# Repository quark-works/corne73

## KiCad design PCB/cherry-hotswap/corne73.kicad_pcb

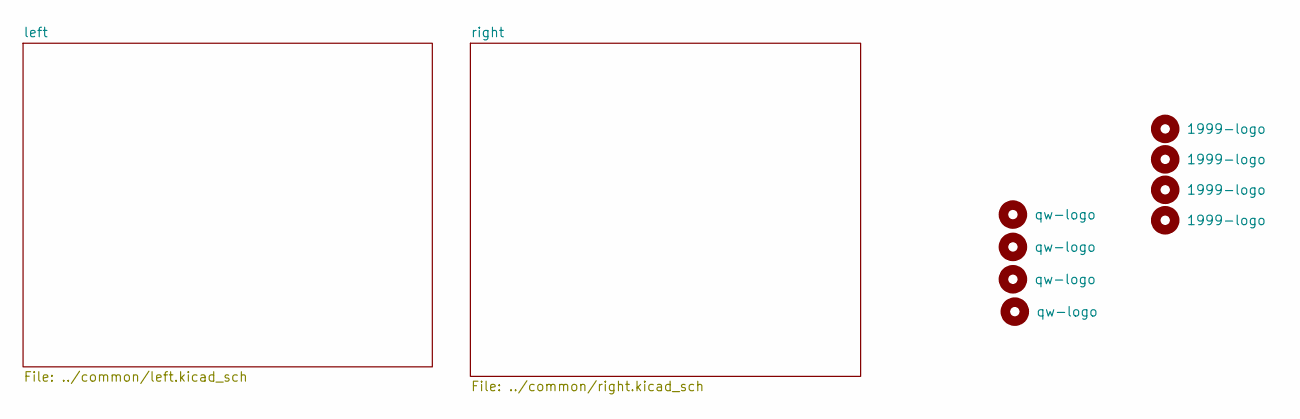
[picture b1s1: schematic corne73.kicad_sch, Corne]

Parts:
H1, H2, H3, H4: qw-logo; qw new logo silk + copper sm
H5, H6, H7, H8: 1999-logo; 1999 logo md

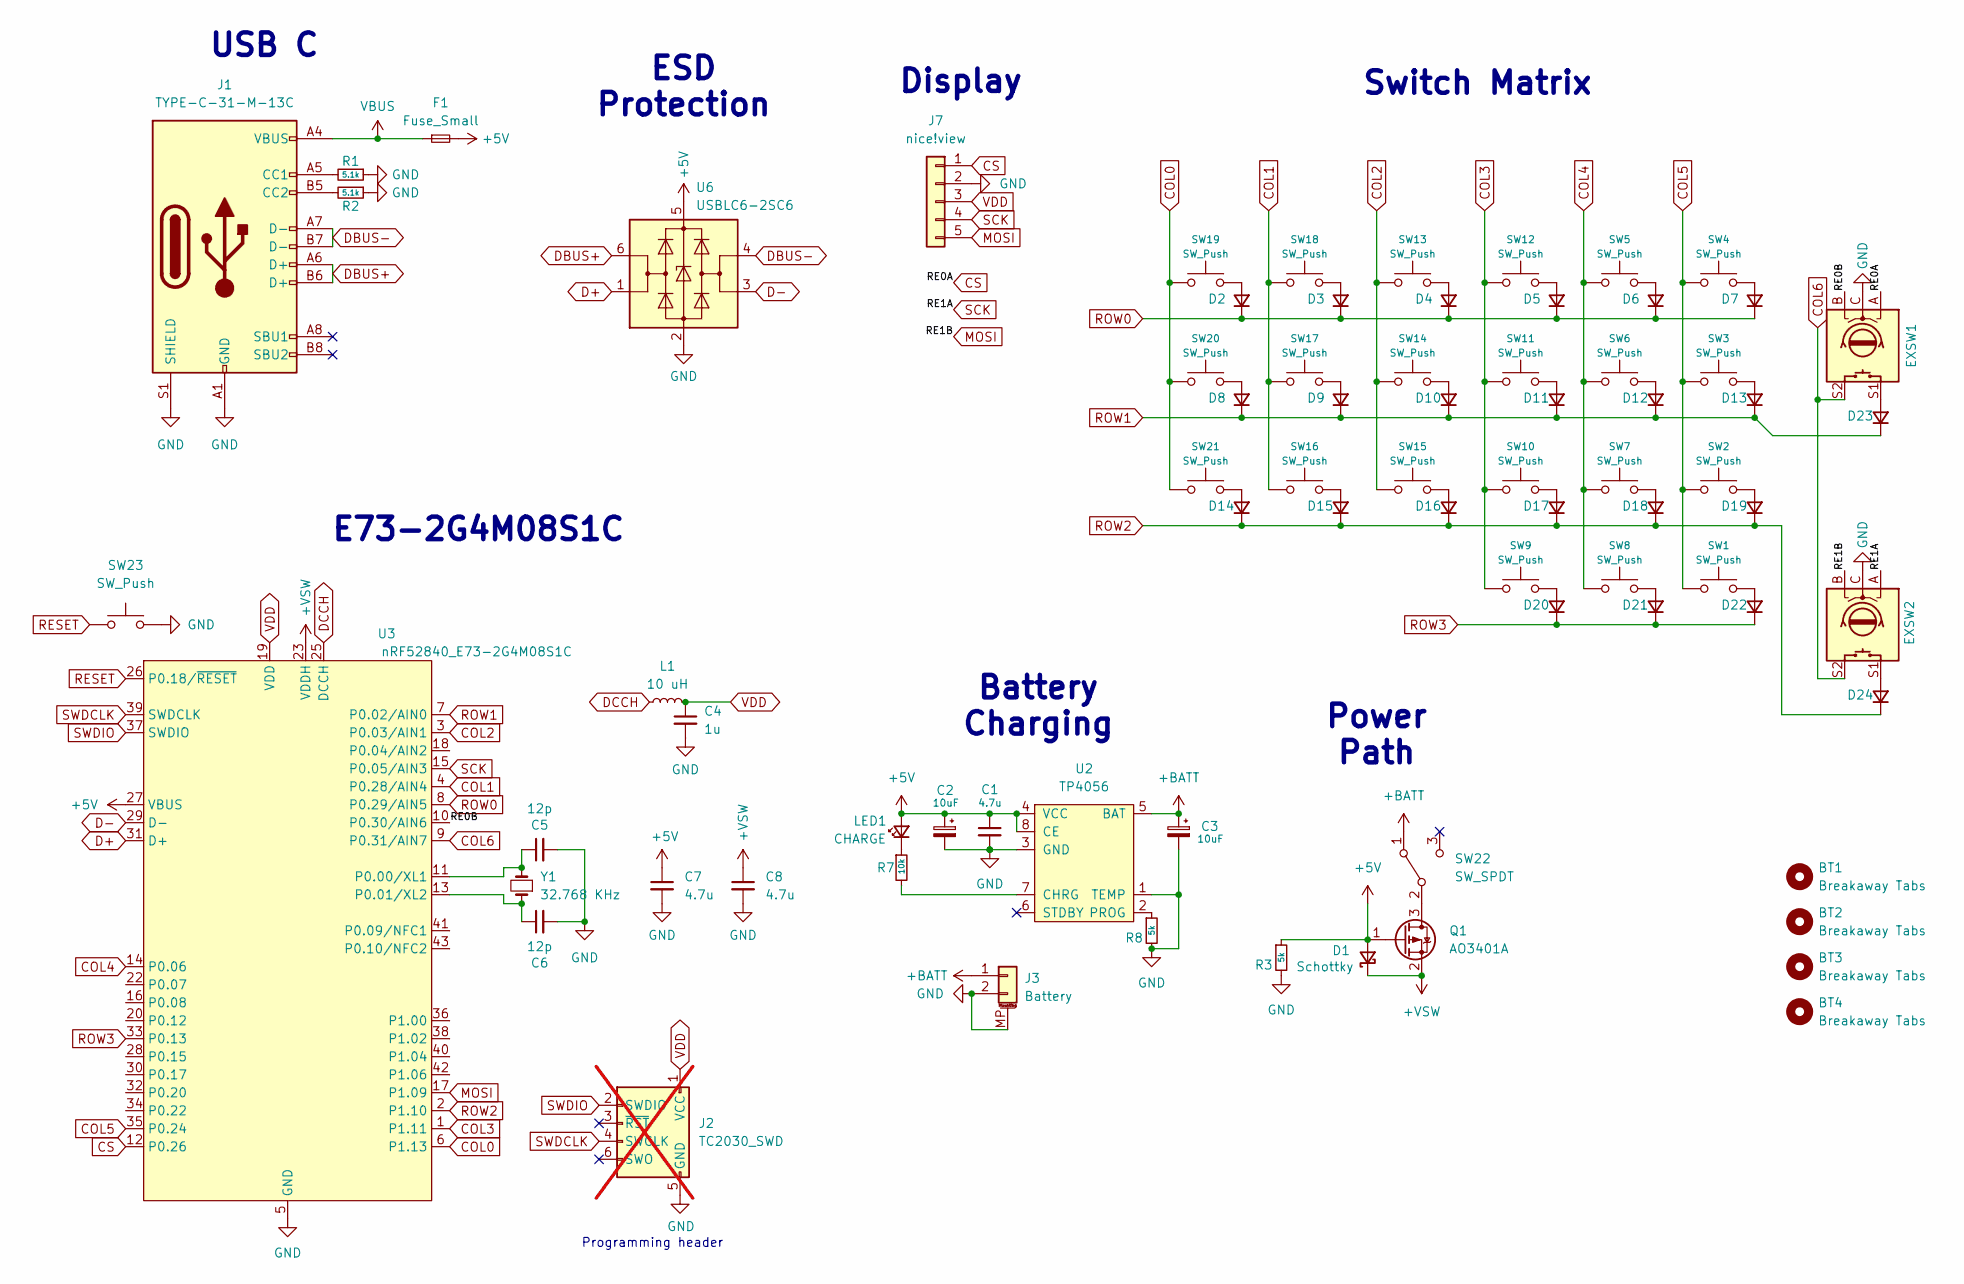
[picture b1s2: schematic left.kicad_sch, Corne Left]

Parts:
BT1, BT2, BT3, BT4: Breakaway Tabs; Breakaway_Tabs
C1, C7, C8: 4.7u; C_0603_1608Metric
C2, C3: 10uF; CP_EIA-2012-12_Kemet-R
C4: 1u; C_0603_1608Metric
C5, C6: 12p; C_0603_1608Metric
D1: Schottky; D_SOD-123
D2, D3, D4, D5, D6, D7, D8, D9, D10, D11, D12, D13, D14, D15, D16, D17, D18, D19, D20, D21, D22, D23, D24: 1N4148; D_SOD-123
EXSW1, EXSW2: RotaryEncoder_Switch; SwitchCombo+Encoder
F1: Fuse_Small; Fuse_1206_3216Metric
J1: TYPE-C-31-M-13C; JLCPCB Part # C2848620
J2: TC2030_SWD; CON_TC2030_outlined; not fitted
J3: Battery; Molex_Pico-EZmate_78171-0002_1x02-1MP_P1.20mm_Vertical
J7: nice!view; PinHeader_1x05_P2.54mm_Vertical
L1: 10 uH; L_0603_1608Metric; LCSC C92982
LED1: CHARGE; LED_0805_2012Metric
Q1: AO3401A; SOT-23
R1, R2: 5.1k; R_0402_1005Metric
R3, R8: 5k; R_0603_1608Metric
R7: 10k; R_0603_1608Metric
SW1, SW2, SW3, SW4, SW5, SW6, SW7, SW8, SW9, SW10, SW11, SW12, SW13, SW14, SW15, SW16, SW17, SW18, SW19, SW20, SW21: SW_Push; SwitchCombo
SW22: SW_SPDT; SW_SPDT_PCM12; LCSC C136720
SW23: SW_Push; SW_T1A2QR
U2: TP4056; CustomTP4056; LCSC C16581
U3: nRF52840_E73-2G4M08S1C; LCSC C356849
U6: USBLC6-2SC6; SOT-23-6
Y1: 32.768 KHz; Crystal_SMD_2012-2Pin_2.0x1.2mm; LCSC C55208

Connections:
+5V: C1.1, C2.1, C7.1, D1.2 (A), F1.2, LED1.2 (A), Q1.1 (G), R3.1, U2.4 (VCC), U2.8 (CE), U3.27 (VBUS), U6.5 (VBUS)
+BATT: C3.1, J3.1, SW22.1 (A), U2.5 (BAT)
+VSW: C8.1, D1.1 (K), Q1.2 (S), U3.23 (VDDH)
/left/RE0B: EXSW1.B, U3.10 (P0.30/AIN6)
COL0: SW19.2, SW20.2, SW21.2, U3.6 (P1.13)
COL1: SW16.2, SW17.2, SW18.2, U3.4 (P0.28/AIN4)
COL2: SW13.2, SW14.2, SW15.2, U3.3 (P0.03/AIN1)
COL3: SW9.2, SW10.2, SW11.2, SW12.2, U3.1 (P1.11)
COL4: SW5.2, SW6.2, SW7.2, SW8.2, U3.14 (P0.06)
COL5: SW1.2, SW2.2, SW3.2, SW4.2, U3.35 (P0.24)
COL6: EXSW1.S2, EXSW2.S2, U3.9 (P0.31/AIN7)
CS: EXSW1.A, J7.1, U3.12 (P0.26)
D+: U3.31 (D+), U6.1 (I/O1)
D-: U3.29 (D-), U6.3 (I/O2)
DBUS+: J1.A6 (D+), J1.B6 (D+), U6.6 (I/O1)
DBUS-: J1.A7 (D-), J1.B7 (D-), U6.4 (I/O2)
DCCH: L1.1, U3.25 (DCCH)
GND: C1.2, C2.2, C3.2, C4.2, C5.2, C6.2, C7.2, C8.2, EXSW1.C, EXSW2.C, J1.A1 (GND), J1.A12 (GND), J1.B1 (GND), J1.B12 (GND), J1.S1 (SHIELD), J2.5 (GND), J3.2, J3.MP (MountPin), J7.2, R1.1, R2.1, R3.2, R8.2, SW23.2, U2.1 (TEMP), U2.3 (GND), U3.5 (GND), U3.21 (GND), U3.24 (GND), U6.2 (GND)
MOSI: EXSW2.B, J7.5, U3.17 (P1.09)
unnamed: D2.2 (A), SW19.1
unnamed: D3.2 (A), SW18.1
unnamed: D4.2 (A), SW13.1
unnamed: D5.2 (A), SW12.1
unnamed: D6.2 (A), SW5.1
unnamed: D7.2 (A), SW4.1
unnamed: D8.2 (A), SW20.1
unnamed: D9.2 (A), SW17.1
unnamed: D10.2 (A), SW14.1
unnamed: D11.2 (A), SW11.1
unnamed: D12.2 (A), SW6.1
unnamed: D13.2 (A), SW3.1
unnamed: D14.2 (A), SW21.1
unnamed: D15.2 (A), SW16.1
unnamed: D16.2 (A), SW15.1
unnamed: D17.2 (A), SW10.1
unnamed: D18.2 (A), SW7.1
unnamed: D19.2 (A), SW2.1
unnamed: D20.2 (A), SW9.1
unnamed: D21.2 (A), SW8.1
unnamed: D22.2 (A), SW1.1
unnamed: D23.2 (A), EXSW1.S1
unnamed: D24.2 (A), EXSW2.S1
unnamed: J1.A5 (CC1), R1.2
unnamed: J1.B5 (CC2), R2.2
unnamed: LED1.1 (K), R7.1
unnamed: Q1.3 (D), SW22.2 (B)
unnamed: R7.2, U2.7 (CHRG)
unnamed: R8.1, U2.2 (PROG)
unnamed: C5.1, U3.11 (P0.00/XL1), Y1.2
unnamed: C6.1, U3.13 (P0.01/XL2), Y1.1
RESET: SW23.1, U3.26 (P0.18/~RESET)
ROW0: D2.1 (K), D3.1 (K), D4.1 (K), D5.1 (K), D6.1 (K), D7.1 (K), U3.8 (P0.29/AIN5)
ROW1: D8.1 (K), D9.1 (K), D10.1 (K), D11.1 (K), D12.1 (K), D13.1 (K), D23.1 (K), U3.7 (P0.02/AIN0)
ROW2: D14.1 (K), D15.1 (K), D16.1 (K), D17.1 (K), D18.1 (K), D19.1 (K), D24.1 (K), U3.2 (P1.10)
ROW3: D20.1 (K), D21.1 (K), D22.1 (K), U3.33 (P0.13)
SCK: EXSW2.A, J7.4, U3.15 (P0.05/AIN3)
SWDCLK: J2.4 (SWCLK), U3.39 (SWDCLK)
SWDIO: J2.2 (SWDIO), U3.37 (SWDIO)
VBUS: F1.1, J1.A4 (VBUS), J1.A9 (VBUS), J1.B4 (VBUS), J1.B9 (VBUS)
VDD: C4.1, J2.1 (VCC), J7.3, L1.2, U3.19 (VDD)

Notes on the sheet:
Display
Power Path
USB C
Battery Charging
Programming header
E73-2G4M08S1C
Switch Matrix
ESD Protection

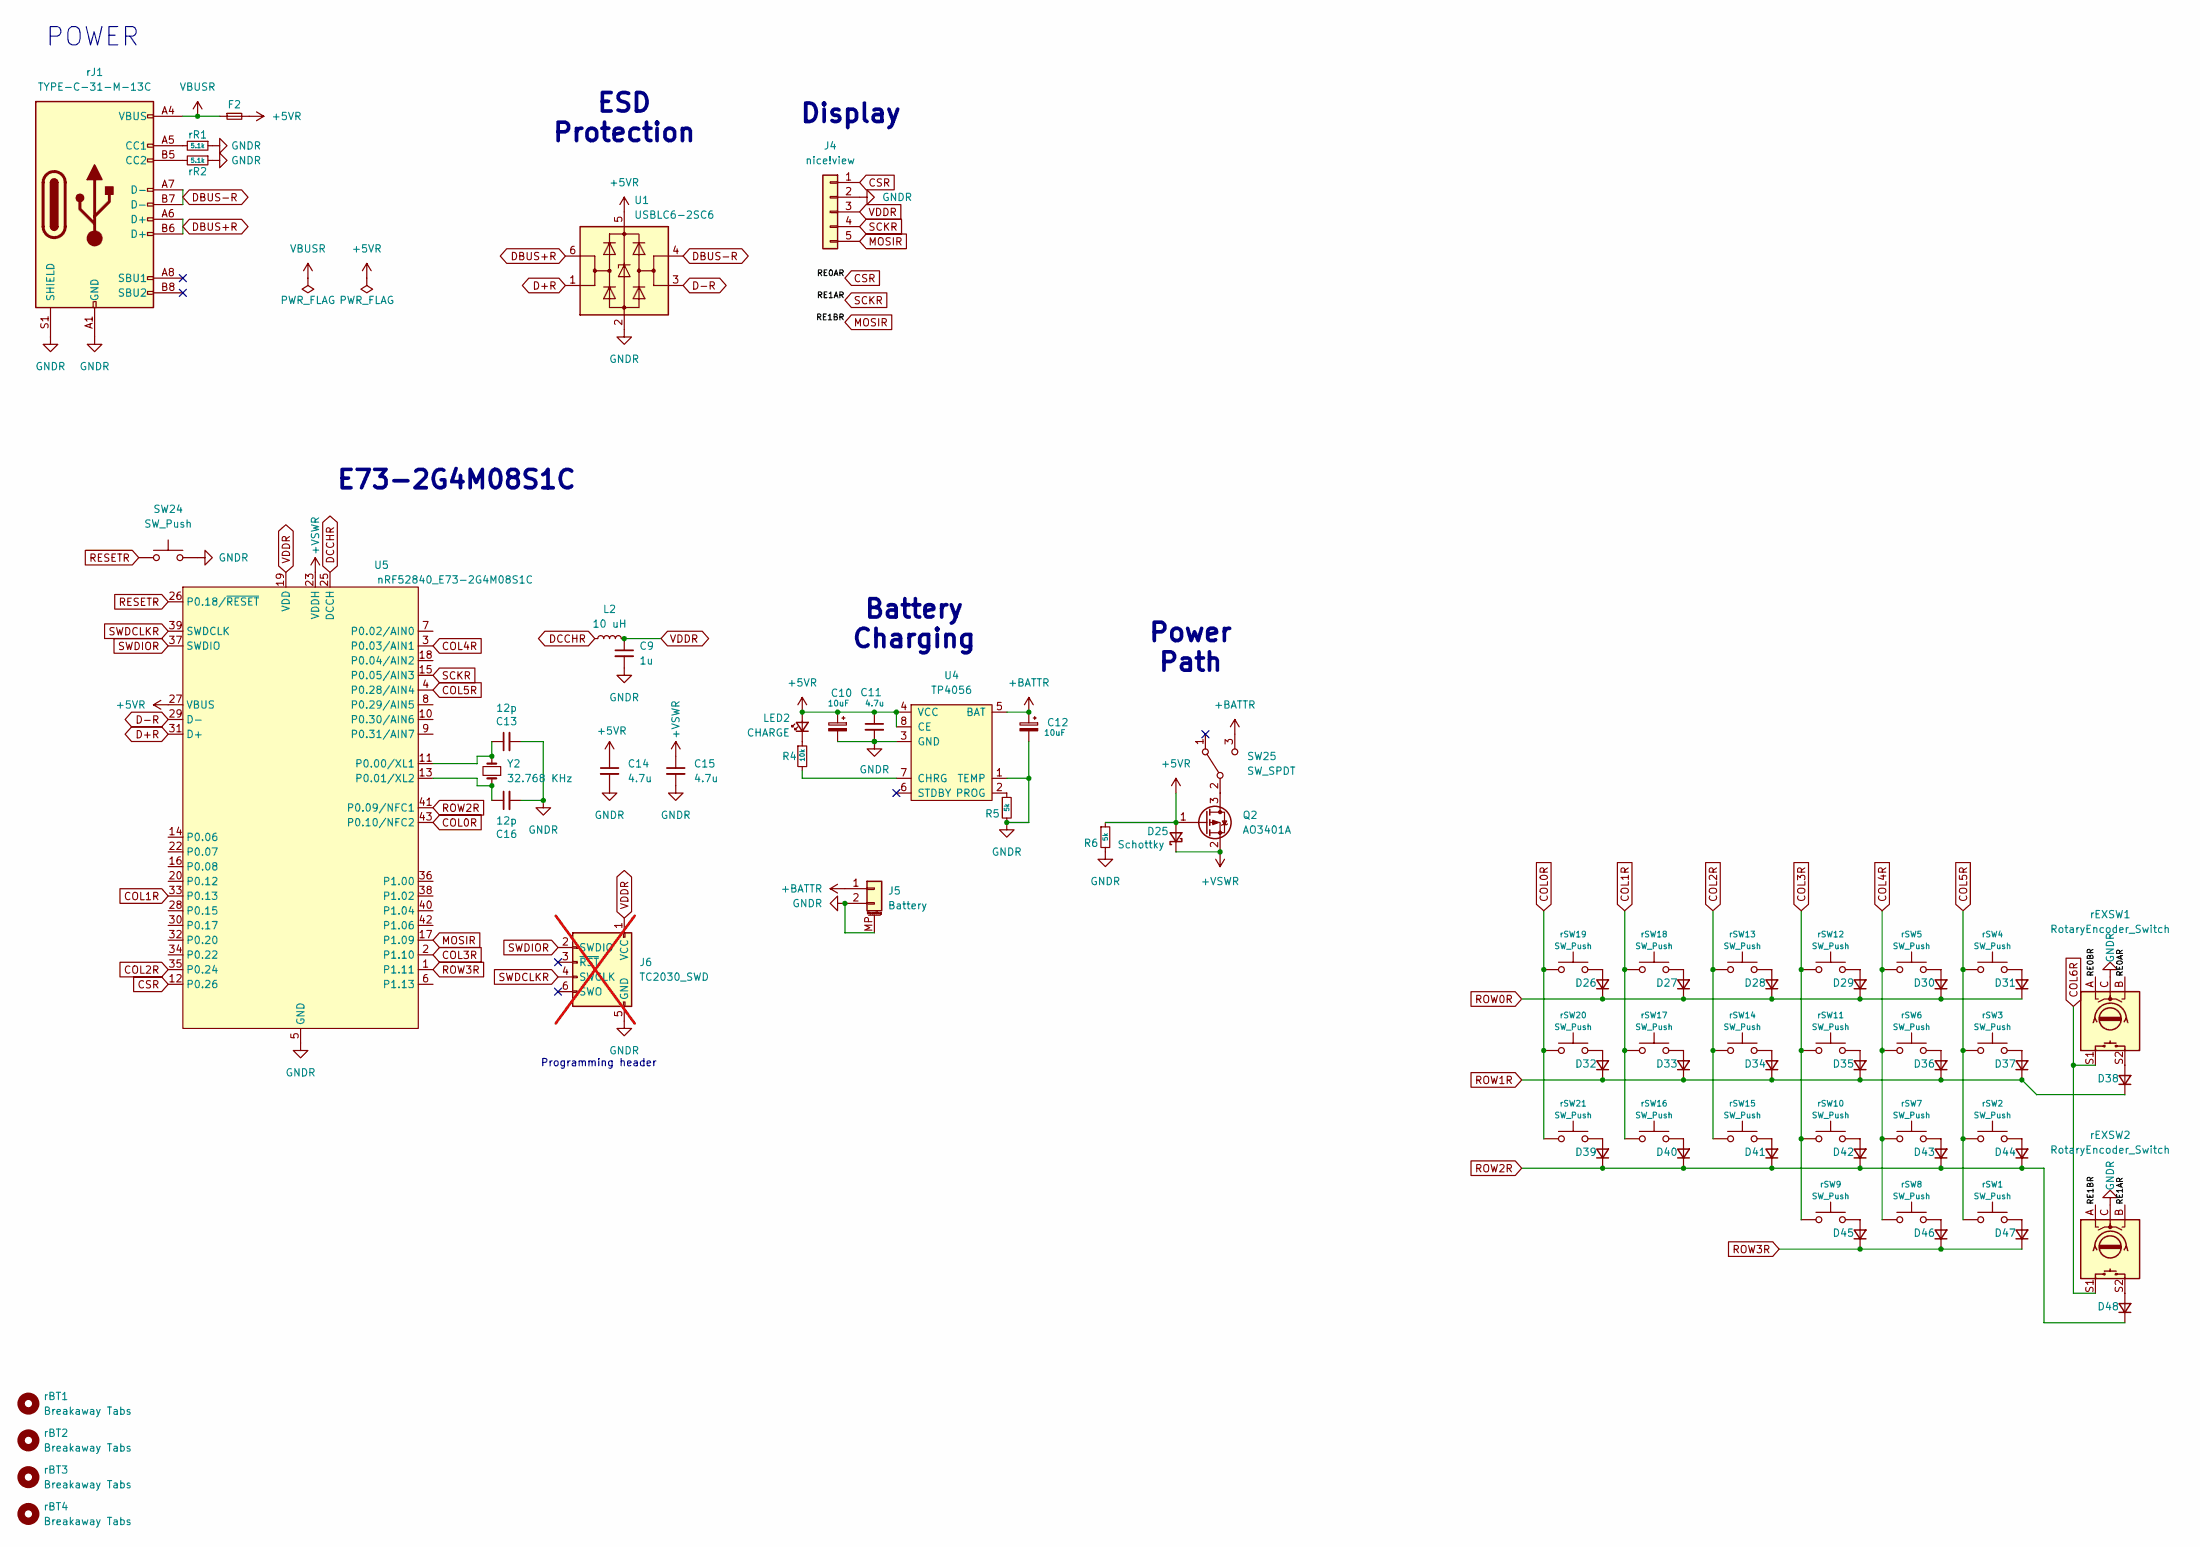
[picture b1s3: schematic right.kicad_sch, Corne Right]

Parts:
C9: 1u; C_0603_1608Metric
C10, C12: 10uF; CP_EIA-2012-12_Kemet-R
C11, C14, C15: 4.7u; C_0603_1608Metric
C13, C16: 12p; C_0603_1608Metric
D25: Schottky; D_SOD-123
D26, D27, D28, D29, D30, D31, D32, D33, D34, D35, D36, D37, D38, D39, D40, D41, D42, D43, D44, D45, D46, D47, D48: 1N4148; D_SOD-123
F2: Fuse_Small; Fuse_1206_3216Metric
J4: nice!view; PinHeader_1x05_P2.54mm_Vertical
J5: Battery; Molex_Pico-EZmate_78171-0002_1x02-1MP_P1.20mm_Vertical
J6: TC2030_SWD; CON_TC2030_outlined; not fitted
L2: 10 uH; L_0603_1608Metric; LCSC C92982
LED2: CHARGE; LED_0805_2012Metric
Q2: AO3401A; SOT-23
R4: 10k; R_0603_1608Metric
R5, R6: 5k; R_0603_1608Metric
SW24: SW_Push; SW_T1A2QR
SW25: SW_SPDT; SW_SPDT_PCM12; LCSC C136720
U1: USBLC6-2SC6; SOT-23-6
U4: TP4056; CustomTP4056; LCSC C16581
U5: nRF52840_E73-2G4M08S1C; LCSC C356849
Y2: 32.768 KHz; Crystal_SMD_2012-2Pin_2.0x1.2mm; LCSC C55208
rBT1, rBT2, rBT3, rBT4: Breakaway Tabs; Breakaway_Tabs
rEXSW1, rEXSW2: RotaryEncoder_Switch; SwitchCombo+Encoder
rJ1: TYPE-C-31-M-13C; JLCPCB Part # C2848620
rR1, rR2: 5.1k; R_0402_1005Metric
rSW1, rSW2, rSW3, rSW4, rSW5, rSW6, rSW7, rSW8, rSW9, rSW10, rSW11, rSW12, rSW13, rSW14, rSW15, rSW16, rSW17, rSW18, rSW19, rSW20, rSW21: SW_Push; SwitchCombo

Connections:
+5VR: C10.1, C11.1, C14.1, D25.2 (A), F2.2, LED2.2 (A), Q2.1 (G), R6.1, U1.5 (VBUS), U4.4 (VCC), U4.8 (CE), U5.27 (VBUS)
+BATTR: C12.1, J5.1, SW25.3 (C), U4.5 (BAT)
+VSWR: C15.1, D25.1 (K), Q2.2 (S), U5.23 (VDDH)
/right/RE0BR: rEXSW1.A
COL0R: U5.43 (P0.10/NFC2), rSW19.2, rSW20.2, rSW21.2
COL1R: U5.33 (P0.13), rSW16.2, rSW17.2, rSW18.2
COL2R: U5.35 (P0.24), rSW13.2, rSW14.2, rSW15.2
COL3R: U5.2 (P1.10), rSW9.2, rSW10.2, rSW11.2, rSW12.2
COL4R: U5.3 (P0.03/AIN1), rSW5.2, rSW6.2, rSW7.2, rSW8.2
COL5R: U5.4 (P0.28/AIN4), rSW1.1, rSW2.2, rSW3.2, rSW4.2
COL6R: rEXSW1.S1, rEXSW2.S1
CSR: J4.1, U5.12 (P0.26), rEXSW1.B
D+R: U1.1 (I/O1), U5.31 (D+)
D-R: U1.3 (I/O2), U5.29 (D-)
DBUS+R: U1.6 (I/O1), rJ1.A6 (D+), rJ1.B6 (D+)
DBUS-R: U1.4 (I/O2), rJ1.A7 (D-), rJ1.B7 (D-)
DCCHR: L2.1, U5.25 (DCCH)
GNDR: C9.2, C10.2, C11.2, C12.2, C13.2, C14.2, C15.2, C16.2, J4.2, J5.2, J5.MP (MountPin), J6.5 (GND), R5.2, R6.2, SW24.2, U1.2 (GND), U4.1 (TEMP), U4.3 (GND), U5.5 (GND), U5.21 (GND), U5.24 (GND), rEXSW1.C, rEXSW2.C, rJ1.A1 (GND), rJ1.A12 (GND), rJ1.B1 (GND), rJ1.B12 (GND), rJ1.S1 (SHIELD), rR1.1, rR2.1
MOSIR: J4.5, U5.17 (P1.09), rEXSW2.A
unnamed: D26.2 (A), rSW19.1
unnamed: D27.2 (A), rSW18.1
unnamed: D28.2 (A), rSW13.1
unnamed: D29.2 (A), rSW12.1
unnamed: D30.2 (A), rSW5.1
unnamed: D31.2 (A), rSW4.1
unnamed: D32.2 (A), rSW20.1
unnamed: D33.2 (A), rSW17.1
unnamed: D34.2 (A), rSW14.1
unnamed: D35.2 (A), rSW11.1
unnamed: D36.2 (A), rSW6.1
unnamed: D37.2 (A), rSW3.1
unnamed: D38.2 (A), rEXSW1.S2
unnamed: D39.2 (A), rSW21.1
unnamed: D40.2 (A), rSW16.1
unnamed: D41.2 (A), rSW15.1
unnamed: D42.2 (A), rSW10.1
unnamed: D43.2 (A), rSW7.1
unnamed: D44.2 (A), rSW2.1
unnamed: D45.2 (A), rSW9.1
unnamed: D46.2 (A), rSW8.1
unnamed: D47.2 (A), rSW1.2
unnamed: D48.2 (A), rEXSW2.S2
unnamed: LED2.1 (K), R4.1
unnamed: Q2.3 (D), SW25.2 (B)
unnamed: R4.2, U4.7 (CHRG)
unnamed: R5.1, U4.2 (PROG)
unnamed: C13.1, U5.11 (P0.00/XL1), Y2.2
unnamed: C16.1, U5.13 (P0.01/XL2), Y2.1
unnamed: rJ1.A5 (CC1), rR1.2
unnamed: rJ1.B5 (CC2), rR2.2
RESETR: SW24.1, U5.26 (P0.18/~RESET)
ROW0R: D26.1 (K), D27.1 (K), D28.1 (K), D29.1 (K), D30.1 (K), D31.1 (K)
ROW1R: D32.1 (K), D33.1 (K), D34.1 (K), D35.1 (K), D36.1 (K), D37.1 (K), D38.1 (K)
ROW2R: D39.1 (K), D40.1 (K), D41.1 (K), D42.1 (K), D43.1 (K), D44.1 (K), D48.1 (K), U5.41 (P0.09/NFC1)
ROW3R: D45.1 (K), D46.1 (K), D47.1 (K), U5.1 (P1.11)
SCKR: J4.4, U5.15 (P0.05/AIN3), rEXSW2.B
SWDCLKR: J6.4 (SWCLK), U5.39 (SWDCLK)
SWDIOR: J6.2 (SWDIO), U5.37 (SWDIO)
VBUSR: F2.1, rJ1.A4 (VBUS), rJ1.A9 (VBUS), rJ1.B4 (VBUS), rJ1.B9 (VBUS)
VDDR: C9.1, J4.3, J6.1 (VCC), L2.2, U5.19 (VDD)

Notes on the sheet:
Display
Power Path
POWER
Battery Charging
E73-2G4M08S1C
Programming header
ESD Protection

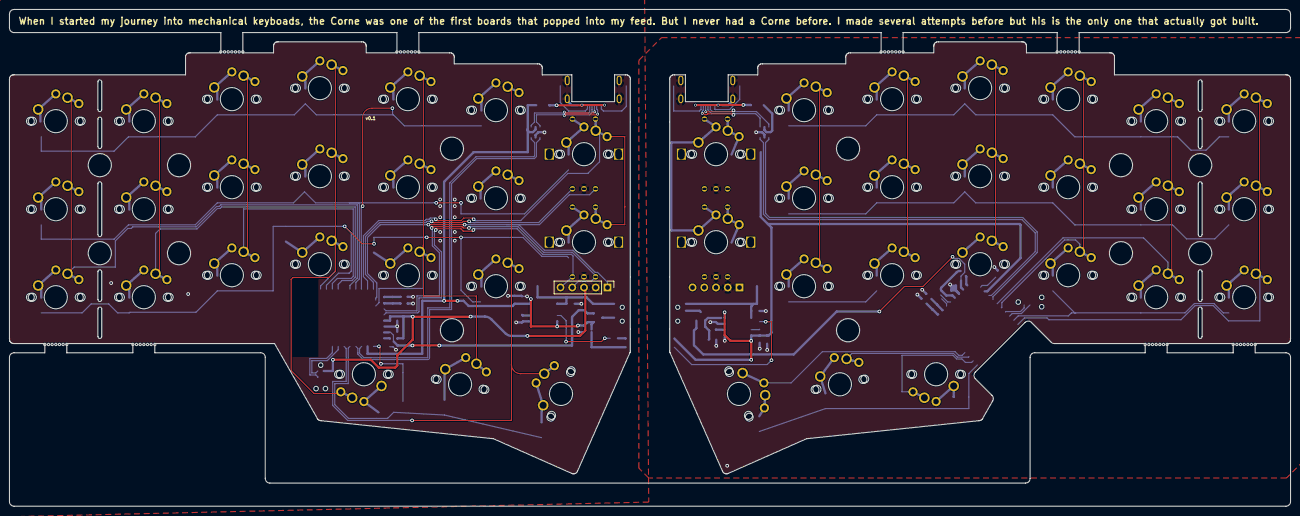
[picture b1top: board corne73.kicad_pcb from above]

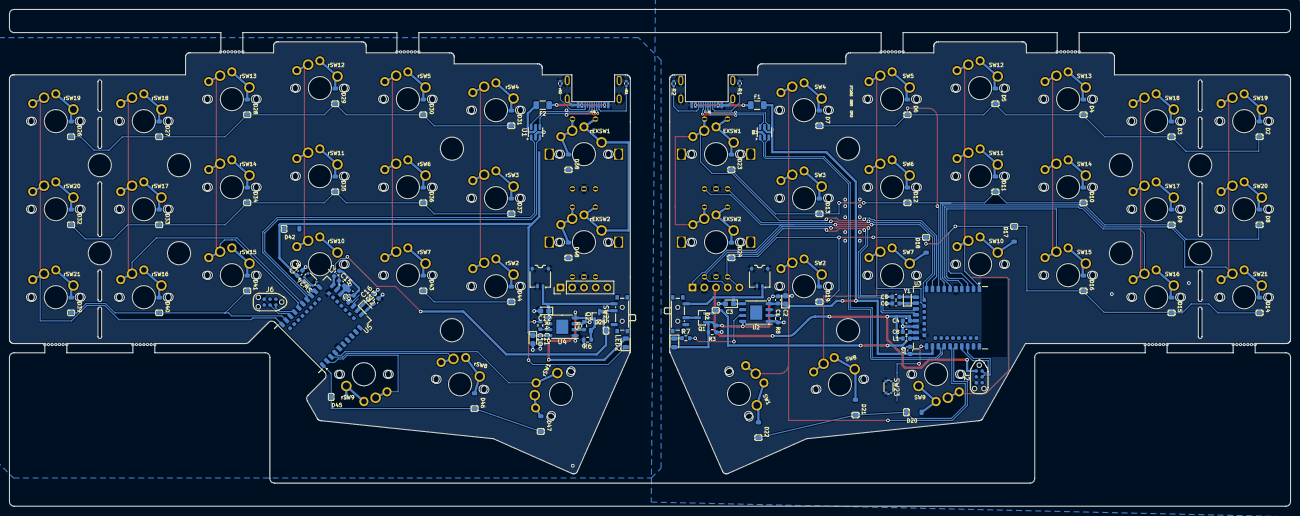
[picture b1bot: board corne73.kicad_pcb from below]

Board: 2 copper layers, 277.2 x 107.5 mm, 164 parts (109 on the bottom side), 119 nets.
